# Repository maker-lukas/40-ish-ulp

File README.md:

# 40%ish ulp

> A split wireless 36 key keyboard powered by the Seeed XIAO Nrf52840 with cherry ULP switches.

<div>
  
</div>

<div>
  
</div>

<div align="center">
  
</div>

---

**40%ish** ulp is a split, ultra low profile keyboard with a 36 key layout, which is great when you are traveling or like a clean and slim build on your desk. It's only 8.25mm thick, with a huge battery so you won't have to charge it every day. It even has a status LED to tell you when the battery is low. Being wireless, it can connect to any device. Using ZMK firmware, you can customize your layout on the fly inside your browser, and its really power efficient!

---

## Features

- 36 key split layout
- Wireless BLE with ZMK
- Cherry ULP switches
- Reversible PCB design

---

## BOM
 
| Part | Qty | Specification | Price | Link |
|------|-----|---------------|-------|------|
| MCU | 2 | Seeed XIAO nRF52840 | $26.18 | [mauser.pt](https://mauser.pt/095-1482/seeed-102010448-microcontrolador-seeed-studio-xiao-nrf52840-c-bluetooth-5-0-ble-nfc-e-carregamento-de-bateria) |
| Switches (pack of 10) | 4 | Cherry ULP | $41.63 | [keeb.supply](https://keeb.supply/products/cherry-mx-ulp?variant=a840d9fa-f4e0-4218-be04-4d0f5e8f7554) |
| PCBs | 5 | Reversible, MOQ 5 | $11.06 | [jlcpcb.com](https://jlcpcb.com) |
| Batteries | 2 | 307095, 5000mAh battery | $16.23 | [aliexpress.com](https://pt.aliexpress.com/item/1005009973979747.html) |
| Diodes | 36 | SOD-123 | $1.57 | [aliexpress.com](https://pt.aliexpress.com/item/1005012163356976.html) |
| Power Switch | 2 | MK-12C02 | $0.87 | [aliexpress.com](https://pt.aliexpress.com/item/1005011530988236.html) |
| Reset Switch | 2 | EVQ-PUL02K | $1.87 | [aliexpress.com](https://pt.aliexpress.com/item/1005010726427079.html) |
| LEDs | 2 | WS2812B | $1.14 | [aliexpress.com](https://pt.aliexpress.com/item/1005008739048100.html) |
| Case | 2 | | $6.42 | [jlc3dp.com](https://jlc3dp.com) |
| Keycaps | 36 | Resin Printed | $37.46 | [jlc3dp.com](https://jlc3dp.com) |
| Magnets | 8 | 5x2mm round magnets | $2.88 | [aliexpress.com](https://pt.aliexpress.com/item/1005009605352565.html) |
| **Total** | | | **$147.31** | |

---

## Soldering notes

Because the PCB is reversible, some of the pins need to be reversed by bridging solder jumpers. Solder all 5 points shown in the images below for each side.

| Left | Right |
|:---:|:---:|
|  |  |

---

## Pictures

| |
|:---:|
| **Blueprint**<br><br> |
| **Schematic**<br><br> |
| **PCB**<br><br> |
| **Zine**<br><br><br>[Full PDF](assets/zine.pdf) |

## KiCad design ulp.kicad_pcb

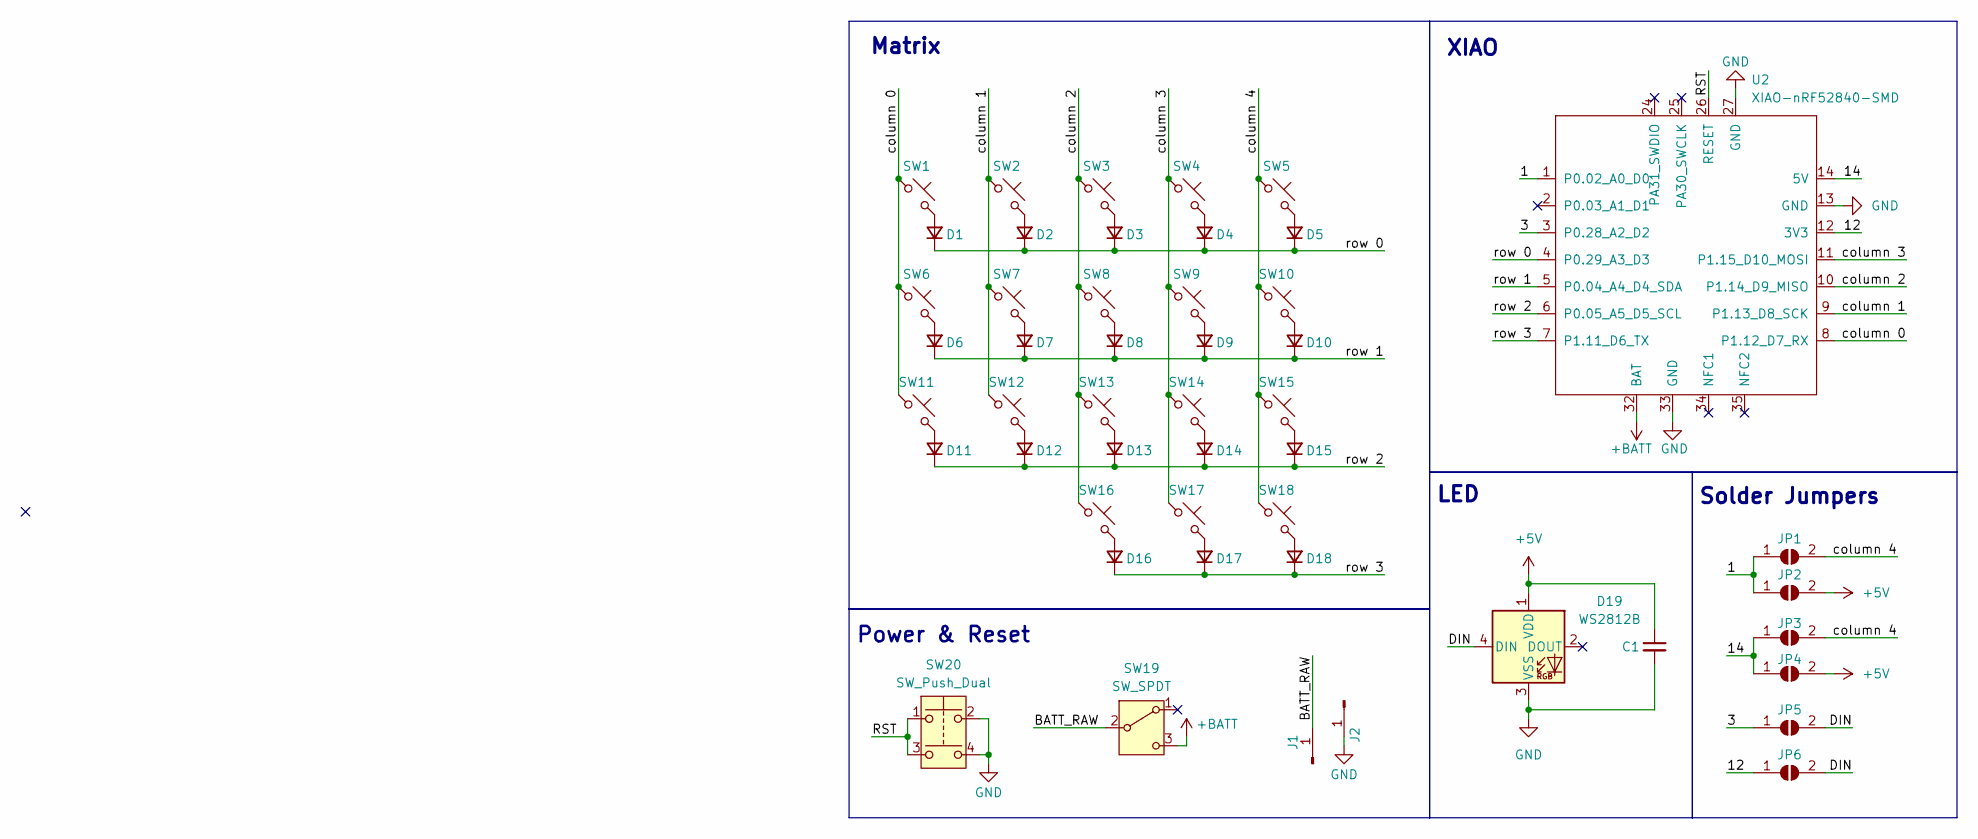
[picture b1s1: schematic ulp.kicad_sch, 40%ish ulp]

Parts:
C1: C_Small; C_0603_1608Metric_Reversible
D1, D2, D3, D4, D5, D6, D7, D8, D9, D10, D11, D12, D13, D14, D15, D16, D17, D18: D_Small; D_SOD-123_Reversible
D19: WS2812B; LED_WS2812B_PLCC4_5.0x5.0mm_P3.2mm_Reversible
J1, J2: Conn_01x01_Pin; TestPoint_Pad_2.0x4.0mm_Reversible
JP1, JP2, JP3, JP4, JP5, JP6: SolderJumper_2_Open; SolderJumper-2_P1.3mm_Open_RoundedPad1.0x1.5mm
SW1, SW2, SW3, SW4, SW5, SW6, SW7, SW8, SW9, SW10, SW11, SW12, SW13, SW14, SW15, SW16, SW17, SW18: SW_Push_45deg; Cherry_ULP_SMD_Double_Sided
SW19: SW_SPDT; SW_SPDT_MSK-12C02_Reversible
SW20: SW_Push_Dual; SW_Push_SPST_EVQ-PU_Reversible
U2: XIAO-nRF52840-SMD; MODULE_Seeed_XIAO_nRF52840_THT_Reversible

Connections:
+5V: C1.1, D19.1 (VDD), JP2.2 (B), JP4.2 (B)
+BATT: SW19.3 (C), U2.32 (BAT)
/1: JP1.1 (A), JP2.1 (A), U2.1 (P0.02_A0_D0)
/3: JP5.1 (A), U2.3 (P0.28_A2_D2)
/12: JP6.1 (A), U2.12 (3V3)
/14: JP3.1 (A), JP4.1 (A), U2.14 (5V)
/BATT_RAW: J1.1 (Pin_1_1), SW19.2 (B)
/DIN: D19.4 (DIN), JP5.2 (B), JP6.2 (B)
/RST: SW20.1, SW20.3, U2.26 (RESET)
/column 0: SW1.1, SW6.1, SW11.1, U2.8 (P1.12_D7_RX)
/column 1: SW2.1, SW7.1, SW12.1, U2.9 (P1.13_D8_SCK)
/column 2: SW3.1, SW8.1, SW13.1, SW16.1, U2.10 (P1.14_D9_MISO)
/column 3: SW4.1, SW9.1, SW14.1, SW17.1, U2.11 (P1.15_D10_MOSI)
/column 4: JP1.2 (B), JP3.2 (B), SW5.1, SW10.1, SW15.1, SW18.1
/row 0: D1.1 (K), D2.1 (K), D3.1 (K), D4.1 (K), D5.1 (K), U2.4 (P0.29_A3_D3)
/row 1: D6.1 (K), D7.1 (K), D8.1 (K), D9.1 (K), D10.1 (K), U2.5 (P0.04_A4_D4_SDA)
/row 2: D11.1 (K), D12.1 (K), D13.1 (K), D14.1 (K), D15.1 (K), U2.6 (P0.05_A5_D5_SCL)
/row 3: D16.1 (K), D17.1 (K), D18.1 (K), U2.7 (P1.11_D6_TX)
GND: C1.2, D19.3 (VSS), J2.1 (Pin_1_1), SW20.2, SW20.4, U2.13 (GND), U2.27 (GND), U2.33 (GND)
unnamed: D1.2 (A), SW1.2
unnamed: D2.2 (A), SW2.2
unnamed: D3.2 (A), SW3.2
unnamed: D4.2 (A), SW4.2
unnamed: D5.2 (A), SW5.2
unnamed: D6.2 (A), SW6.2
unnamed: D7.2 (A), SW7.2
unnamed: D8.2 (A), SW8.2
unnamed: D9.2 (A), SW9.2
unnamed: D10.2 (A), SW10.2
unnamed: D11.2 (A), SW11.2
unnamed: D12.2 (A), SW12.2
unnamed: D13.2 (A), SW13.2
unnamed: D14.2 (A), SW14.2
unnamed: D15.2 (A), SW15.2
unnamed: D16.2 (A), SW16.2
unnamed: D17.2 (A), SW17.2
unnamed: D18.2 (A), SW18.2

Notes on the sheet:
Matrix
LED
XIAO
Power & Reset
Solder Jumpers

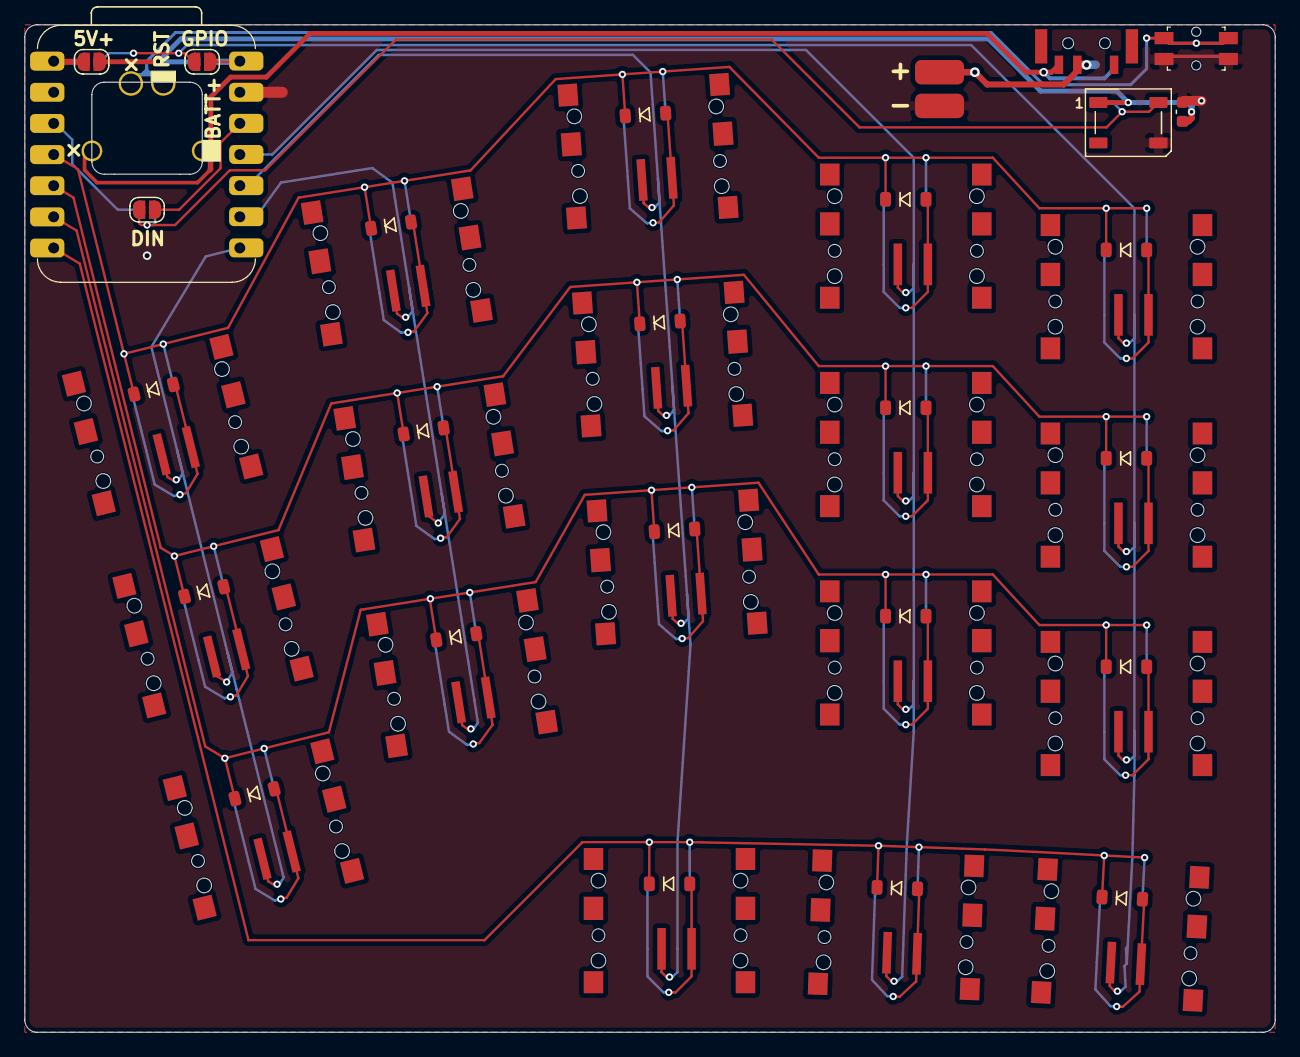
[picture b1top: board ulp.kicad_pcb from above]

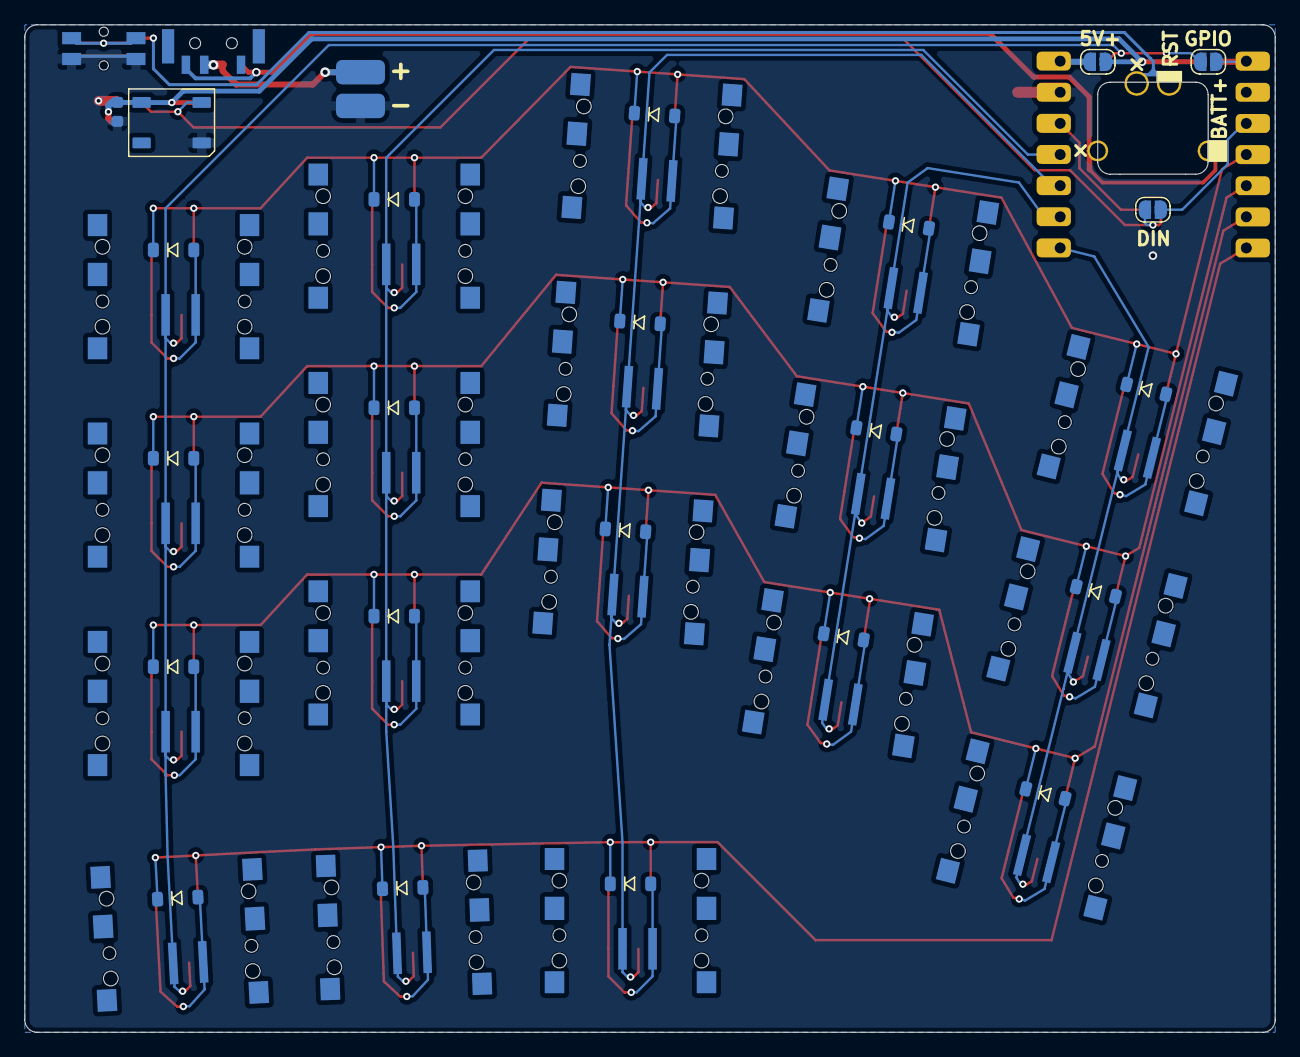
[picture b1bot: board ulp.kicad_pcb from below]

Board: 2 copper layers, 102.0 x 82.2 mm, 49 parts (3 on the bottom side), 37 nets.

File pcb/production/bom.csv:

Designator,Footprint,Quantity,Value,LCSC Part #
C1,0603,1,C_Small,
"D1, D10, D11, D12, D13, D14, D15, D16, D17, D18, D2, D3, D4, D5, D6, D7, D8, D9",D_SOD-123_Reversible,18,D_Small,
D19,LED_WS2812B_PLCC4_5.0x5.0mm_P3.2mm_Reversible,1,WS2812B,
"J1, J2",TestPoint_Pad_2.0x4.0mm_Reversible,2,Conn_01x01_Pin,
"SW1, SW10, SW11, SW12, SW13, SW14, SW15, SW16, SW17, SW18, SW2, SW3, SW4, SW5, SW6, SW7, SW8, SW9",Cherry_ULP_SMD_Double_Sided,18,SW_Push_45deg,
SW19,SW_SPDT_MSK-12C02_Reversible,1,SW_SPDT,C2911519
SW20,SW_Push_SPST_EVQ-PU_Reversible,1,SW_Push_Dual,C79175
U2,MODULE_Seeed_XIAO_nRF52840_THT_Reversible,1,XIAO-nRF52840-SMD,

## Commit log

2026-05-29 add pcb files
2026-05-29 add gitignore with backups folder
2026-05-29 Stop tracking ulp-backups
    Amp-Thread-ID: https://ampcode.com/threads/T-019e7445-9c97-7198-8a44-fdf52582fa4e
2026-05-29 small changes
2026-05-29 remove layer
2026-05-29 Stop tracking ignored files
    Amp-Thread-ID: https://ampcode.com/threads/T-019e7445-9c97-7198-8a44-fdf52582fa4e
2026-05-31 update pcb
2026-05-31 add .step files of each side
2026-05-31 update .step files
2026-05-31 add README.md
2026-05-31 remove file
2026-06-05 change board outline
2026-06-05 test commit
2026-06-06 add new pcb stuff
2026-06-09 Update README with features and BOM
    Added detailed features and BOM for the 40%ush ULP keyboard.
2026-06-09 Update prices and links for power and reset switches
2026-06-09 Update keycaps entry with material and price
2026-06-09 Add price and link for WS2812B LEDs
2026-06-10 add mounting holes and new models
2026-06-10 restructure repo to clean up
2026-06-11 test banner image
2026-06-11 crop banner image
2026-06-11 resize and center banner image
2026-06-11 test uncenterd image
2026-06-11 undo changes
2026-06-12 add zine
2026-06-13 add all case and firmware files
2026-06-14 add new 3D files
2026-06-14 add blueprint
2026-06-14 udpate image table
2026-06-14 untrack ulp-backups directory
2026-06-14 add schematic and PCB images to README
2026-06-15 add production files + update BOM
2026-06-15 adding BOM
2026-06-15 Ignore KiCad library tables and fabrication toolkit options
    Amp-Thread-ID: https://ampcode.com/threads/T-019ecb23-611f-761b-a8e9-f24c43f40df0
2026-06-15 add magnets to BOM
2026-06-16 add kicanvas banner
2026-06-16 make banner bigger
2026-06-16 change size again
2026-06-16 add new size
2026-06-16 add cad banner
2026-06-16 change stuff
2026-06-16 rename images folder to assets
2026-06-16 change images/ to assets/ in README
2026-06-16 add battery pricing and link
2026-06-16 Add CERN Open Hardware Licence Version 2
    Added CERN Open Hardware Licence Version 2 - Strongly Reciprocal to the project.
2026-06-16 fix typo
2026-06-17 add little documentaito on how to solder
